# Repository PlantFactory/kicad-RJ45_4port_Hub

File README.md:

# kicad-RJ45_4port_Hub
I2C 4 port hub via RJ45 board.

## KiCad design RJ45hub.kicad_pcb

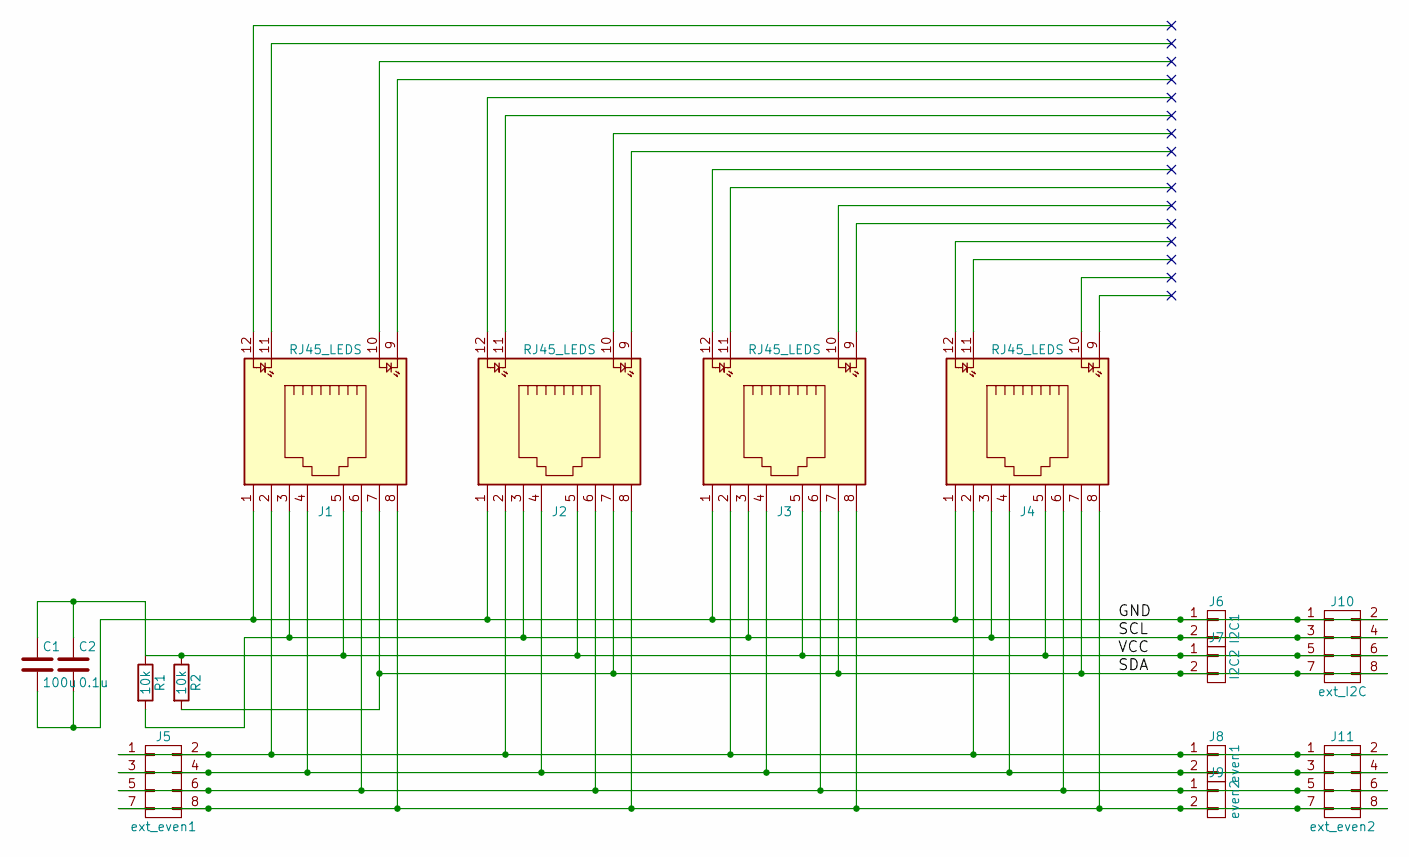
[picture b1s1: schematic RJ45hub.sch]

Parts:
C1: 100u; CP_Radial_D6.3mm_P2.50mm
C2: 0.1u; C_Disc_D3.0mm_W1.6mm_P2.50mm
J1, J2, J3, J4: RJ45_LEDS; NewWays8p8c
J5: ext_even1; Pin_Header_Straight_2x04_Pitch2.54mm
J6: I2C1; TerminalBlock2
J7: I2C2; TerminalBlock2
J8: even1; TerminalBlock2
J9: even2; TerminalBlock2
J10: ext_I2C; Pin_Header_Straight_2x04_Pitch2.54mm
J11: ext_even2; Pin_Header_Straight_2x04_Pitch2.54mm
R1, R2: 10k; R_Axial_DIN0207_L6.3mm_D2.5mm_P10.16mm_Horizontal

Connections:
/GND: C1.2, C2.2, J1.1, J2.1, J3.1, J4.1, J6.1, J10.1, J10.2; also elsewhere on the board
/SCL: J1.3, J2.3, J3.3, J4.3, J6.2, J10.3, J10.4, R1.2
/SDA: J1.7, J2.7, J3.7, J4.7, J7.2, J10.7, J10.8, R2.2
/VCC: C1.1, C2.1, J1.5, J2.5, J3.5, J4.5, J7.1, J10.5, J10.6, R1.1, R2.1
unnamed: J1.2, J2.2, J3.2, J4.2, J5.1, J5.2, J8.1, J11.1, J11.2
unnamed: J1.4, J2.4, J3.4, J4.4, J5.3, J5.4, J8.2, J11.3, J11.4
unnamed: J1.6, J2.6, J3.6, J4.6, J5.5, J5.6, J9.1, J11.5, J11.6
unnamed: J1.8, J2.8, J3.8, J4.8, J5.7, J5.8, J9.2, J11.7, J11.8

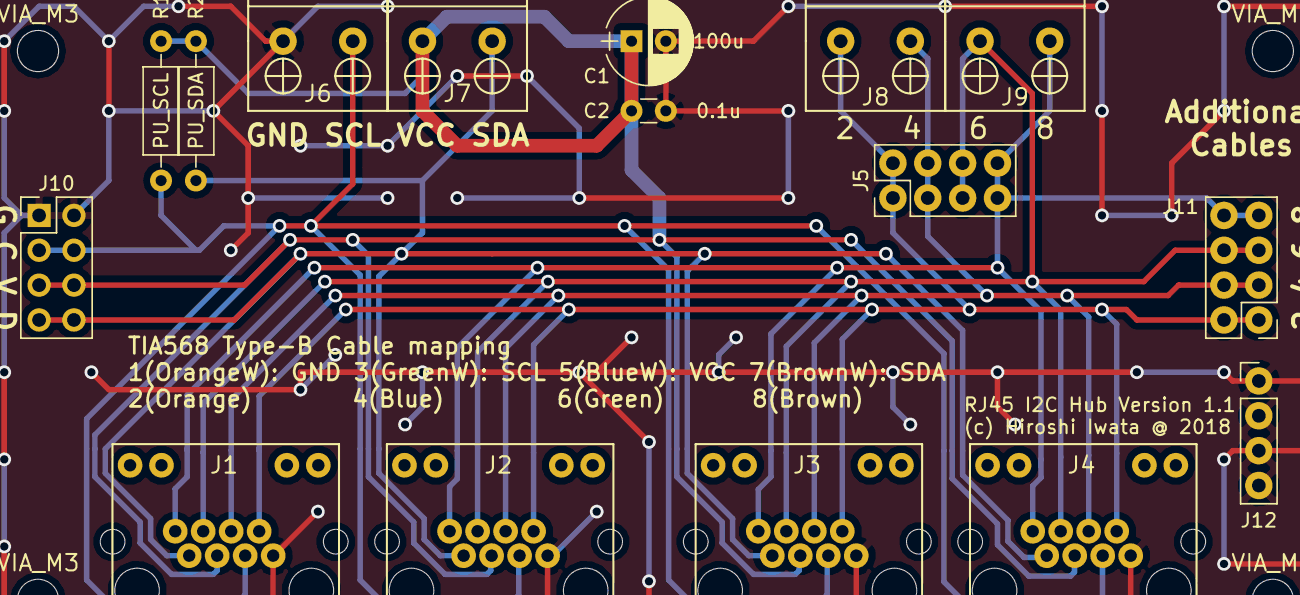
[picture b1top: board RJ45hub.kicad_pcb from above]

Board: 2 copper layers, 20 parts (0 on the bottom side), 8 nets.

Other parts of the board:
J12: Test; Pin_Header_Straight_1x04_Pitch2.54mm
R**: VIA_M3
R**#2, R**#3, R**#4: VIA_M3

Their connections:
/GND: J12.1, J12.2, J12.3, J12.4; also elsewhere on the board
